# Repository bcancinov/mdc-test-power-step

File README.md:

# mdc-test-power-step
Modular Detector Controller Test Power Step Board

## Overview
This board generates controlled load steps at multiple bias rails to evaluate DC/DC module stability, settling, and control-loop bandwidth under different load conditions. It is intended to be used alongside the `mdc-power-*` DC/DC module boards.

## Objective
- Test stability and transient response across different bias rails.
- Measure settling time and bandwidth under programmable load conditions.

## System Context
- DC/DC generation is provided by the `mdc-power-*` boards.
- This board provides load-step capability and measurement access for those rails.
- Board input: 12V.

## Board Stackup
- 4-layer PCB

## Board Dimensions
- 136.4 mm x 105.35 mm

## CAD
- Designed using KiCad 9.

## Key Functions
- Programmable load steps using MOSFET-switched resistor banks.
- Multiple selectable load levels per rail.
- Local support rails and timing (LDO + oscillator) for step control.
- External 3.3V step input for injecting step signals on both positive and negative DUT outputs.
- 2 MHz oscillator to provide a sync reference for the DC-DC DUT.

## Images
Layout:

3D view:

## Load Step Networks (from schematic)
High-power resistors (primary load steps):
- 3.3V: 2 ohm, 6 A, `PWR163S-25-2R00F`
- 6V: 8 ohm, 3 A, `PWR163S-25-8R00F`
- 16V: 120 ohm, 0.5 A, `PWR163S-25-1200F`

Alternate lower-power options (noted on schematic):
- 3.3V: 5.6 ohm, 0.6 A, `LTR100JZPF5R60`
- 6V: 20 ohm, 0.3 A, `LTR100JZPF20R0`
- 16V: 320 ohm, 0.05 A, `LTR100JZPF3300`

## Relevant ICs and Roles
- `U2: LP2980` LDO regulator for local low-power rail.
- `X1: SiT2024B` oscillator for step timing/control.
- `U3/U4: UCC27531D` gate drivers for MOSFET-switched loads.
- `Q1/Q2: ISZ015N04NM7V` power MOSFETs for load switching.

## Signals (from schematic)
- Control and status: `en`, `pg`, `sync`, `en_osc`, `step_pos`

## Files
- Schematic: `test_power_step.pdf`

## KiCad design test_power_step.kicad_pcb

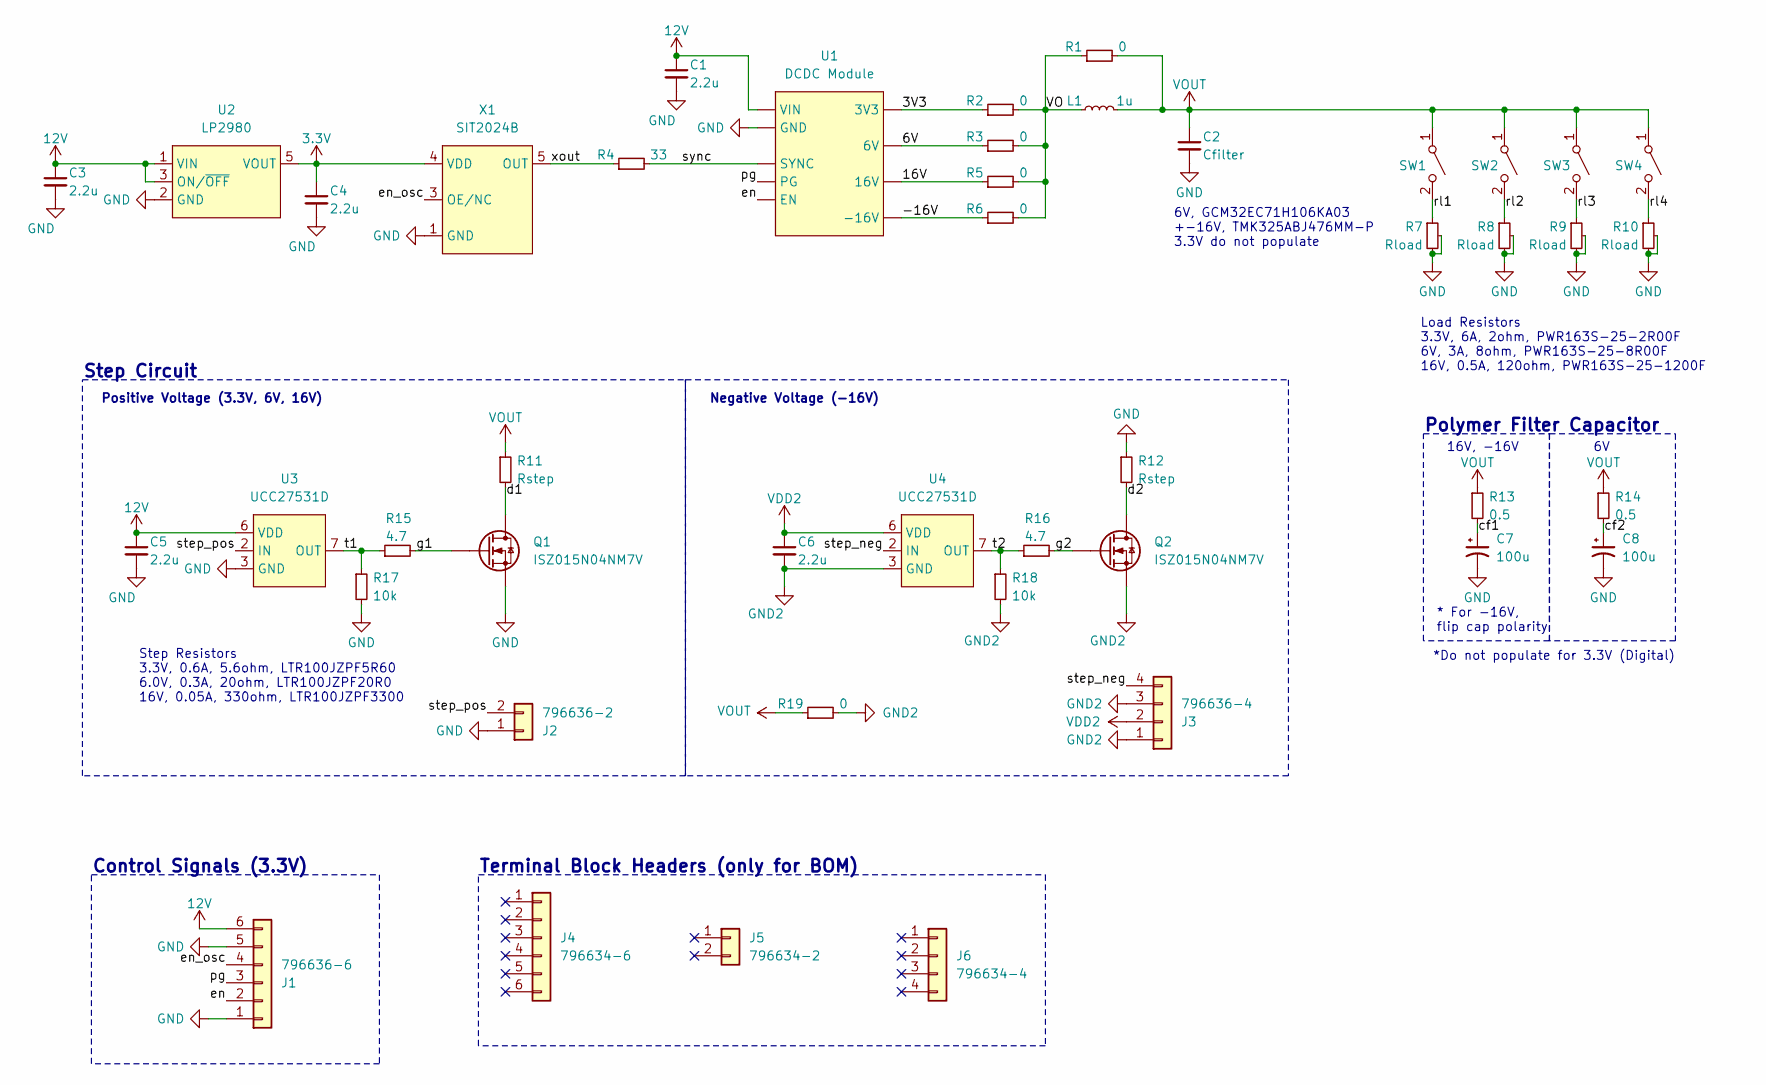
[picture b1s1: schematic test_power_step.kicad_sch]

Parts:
C1, C3, C4, C5, C6: 2.2u; C_0805_2012Metric; MPN C0805C225K5RACAUTO
C2: Cfilter; C_1210_3225Metric
C7: 100u; T521X; MPN T521X107M025ATE060
C8: 100u; T52xL; MPN T520L107M010ATE025
J1: 796636-6; CON6_P5MM_VER_TERM-BLK_TYC; MPN 796636-6
J2: 796636-2; CON2_P5MM_VER_TERM-BLK_TYC; MPN 796636-2
J3: 796636-4; CON4_P5MM_VER_TERM-BLK_TYC; MPN 796636-4
J4: 796634-6; CON6_P5MM_VER_TERM-BLK_TYC; MPN 796634-6
J5: 796634-2; CON2_P5MM_VER_TERM-BLK_TYC; MPN 796634-2
J6: 796634-4; CON4_P5MM_VER_TERM-BLK_TYC; MPN 796634-4
L1: 1u; XGL4020; MPN XGL4020-102MEC
Q1, Q2: ISZ015N04NM7V; TSDSON-8-40; MPN ISZ015N04NM7VATMA1
R1, R2, R3, R5, R6, R19: 0; R_2512_6332Metric; MPN WSL251200000ZEA9
R4: 33; R_0603_1608Metric; MPN CRCW060333R0FKEA
R7, R8, R9, R10: Rload; PWR163
R11, R12: Rstep; R_1225_3264Metric
R13, R14: 0.5; R_0603_1608Metric; MPN RCWE0603R500FKEA
R15, R16: 4.7; R_0603_1608Metric; MPN CRCW06034R70FKEAHP
R17, R18: 10k; R_0603_1608Metric; MPN CRCW060310K0FKEAHP
SW1, SW2, SW3, SW4: SW_SPST; L101; MPN L101121MS02Q
U1: DCDC Module; DCDC_module
U2: LP2980; SOT-23-5; MPN LP2980AIM5-3.3/NOPB
U3, U4: UCC27531D; SOIC-8_3.9x4.9mm_P1.27mm; MPN UCC27531D
X1: SIT2024B; SOT-23-5; MPN SIT2024BM-S1-33E-2.000000

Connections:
3.3V: C4.1, U2.5 (VOUT), X1.4 (VDD)
12V: C1.1, C3.1, C5.1, J1.6, U1.vin (VIN), U2.1 (VIN), U2.3 (ON/~OFF), U3.6 (VDD)
/3V3: R2.1, U1.3v3 (3V3)
/6V: R3.1, U1.6v (6V)
/16V: R5.1, U1.16v (16V)
/-16V: R6.1, U1.-16v (-16V)
/VO: L1.1, R1.1, R2.2, R3.2, R5.2, R6.2
/cf1: C7.1, R13.2
/cf2: C8.1, R14.2
/d1: Q1.D, R11.2
/d2: Q2.D, R12.2
/en: J1.2, U1.en (EN)
/en_osc: J1.4, X1.3 (OE/NC)
/g1: Q1.G, R15.2
/g2: Q2.G, R16.2
/pg: J1.3, U1.pg (PG)
/rl1: R7.1, SW1.2 (B)
/rl2: R8.1, SW2.2 (B)
/rl3: R9.1, SW3.2 (B)
/rl4: R10.1, SW4.2 (B)
/step_neg: J3.4, U4.2 (IN)
/step_pos: J2.2, U3.2 (IN)
/sync: R4.2, U1.sync (SYNC)
/t1: R15.1, R17.1, U3.7 (OUT)
/t2: R16.1, R18.1, U4.7 (OUT)
/xout: R4.1, X1.5 (OUT)
GND: C1.2, C2.2, C3.2, C4.2, C5.2, C7.2, C8.2, J1.1, J1.5, J2.1, Q1.S, R7.2, R7.3, R8.2, R8.3, R9.2, R9.3, R10.2, R10.3, R12.1, R17.2, U1.gnd (GND), U2.2 (GND), U3.3 (GND), X1.1 (GND)
GND2: C6.2, J3.1, J3.3, Q2.S, R18.2, R19.2, U4.3 (GND)
VDD2: C6.1, J3.2, U4.6 (VDD)
VOUT: C2.1, L1.2, R1.2, R11.1, R13.1, R14.1, R19.1, SW1.1 (A), SW2.1 (A), SW3.1 (A), SW4.1 (A)

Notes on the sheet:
Load Resistors 3.3V, 6A, 2ohm, PWR163S-25-2R00F 6V, 3A, 8ohm, PWR163S-25-8R00F 16V, 0.5A, 120ohm, PWR163S-25-1200F
*Do not populate for 3.3V (Digital)
* For -16V, flip cap polarity
Control Signals (3.3V)
Positive Voltage (3.3V, 6V, 16V)
Negative Voltage (-16V)
Polymer Filter Capacitor
Terminal Block Headers (only for BOM)
Step Circuit
Step Resistors 3.3V, 0.6A, 5.6ohm, LTR100JZPF5R60 6.0V, 0.3A, 20ohm, LTR100JZPF20R0 16V, 0.05A, 330ohm, LTR100JZPF3300
16V, -16V
6V, GCM32EC71H106KA03 +-16V, TMK325ABJ476MM-P 3.3V do not populate

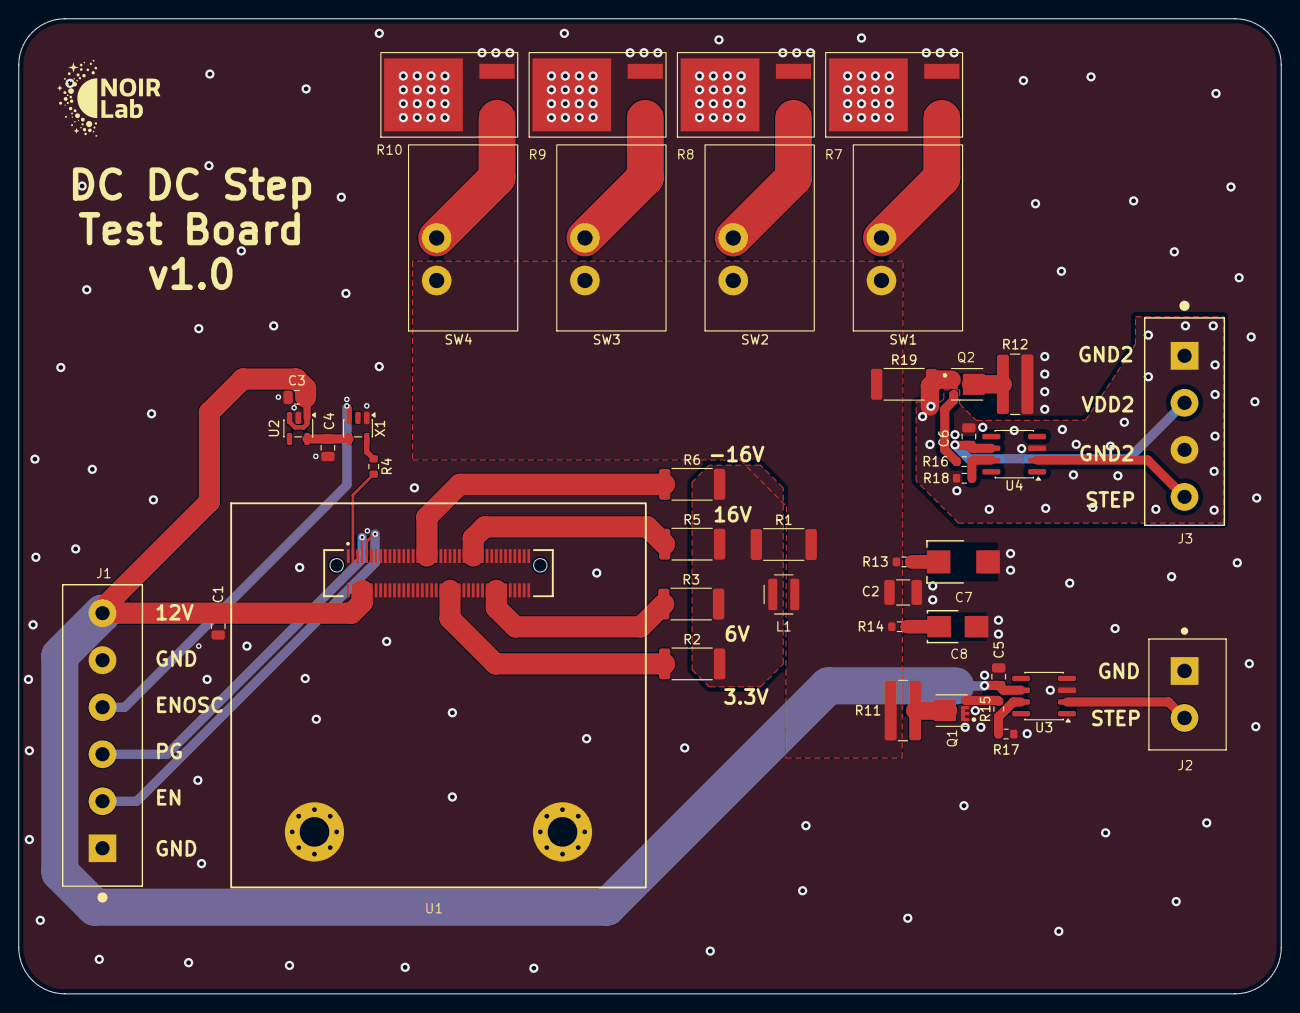
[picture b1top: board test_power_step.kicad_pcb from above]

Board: 4 copper layers, 136.4 x 105.3 mm, 42 parts (0 on the bottom side), 30 nets.

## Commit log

2026-02-06 update readme and docs
